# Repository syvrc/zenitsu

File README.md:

## zenitsu

> I made a zenitsu keychain that has 2 LEDs for its eyes that fade on in the dark with a photoresistor and capacitor, it also has a push button to turn the LEDs off even in the dark.  

## Schematic

# PCB
| PCB Front               | PCB Back                         |
|:-----------------------:|:--------------------------------:|
||  |

## 3d render
| Front                          | Back                          |
|:------------------------------:|:-----------------------------:|
|||

## Features
> it has photoresistor to control when LEDs will be: `ON (dark)` and `OFF (light)`  
> capacitor for a light fade effect on the LEDs  
> a toggle button switch to turn off LEDs even when dark outside  
> its a KEYCHAINN !!!

## BOM
| Component               | Qty |
| ----------------------- | --- |
| LEDs                    | 2   |
| Battery Holder          | 1   |
| Photoresistor           | 1   |
| Potentiometer           | 1   |
| 2.2M Resistor           | 1   |
| 4.7k Resistor           | 1   |
| 47k Resistor            | 1   |
| 100k Resistor           | 1   |
| 220 Resistor            | 1   |
| 470 Resistors           | 2   |
| 10uF Capacitor          | 1   |
| 470nF Capacitor         | 1   |
| Push Button             | 1   |
| NPN Transistors         | 3   |

---
> made by @syvr (on slack) 🚶‍♂️

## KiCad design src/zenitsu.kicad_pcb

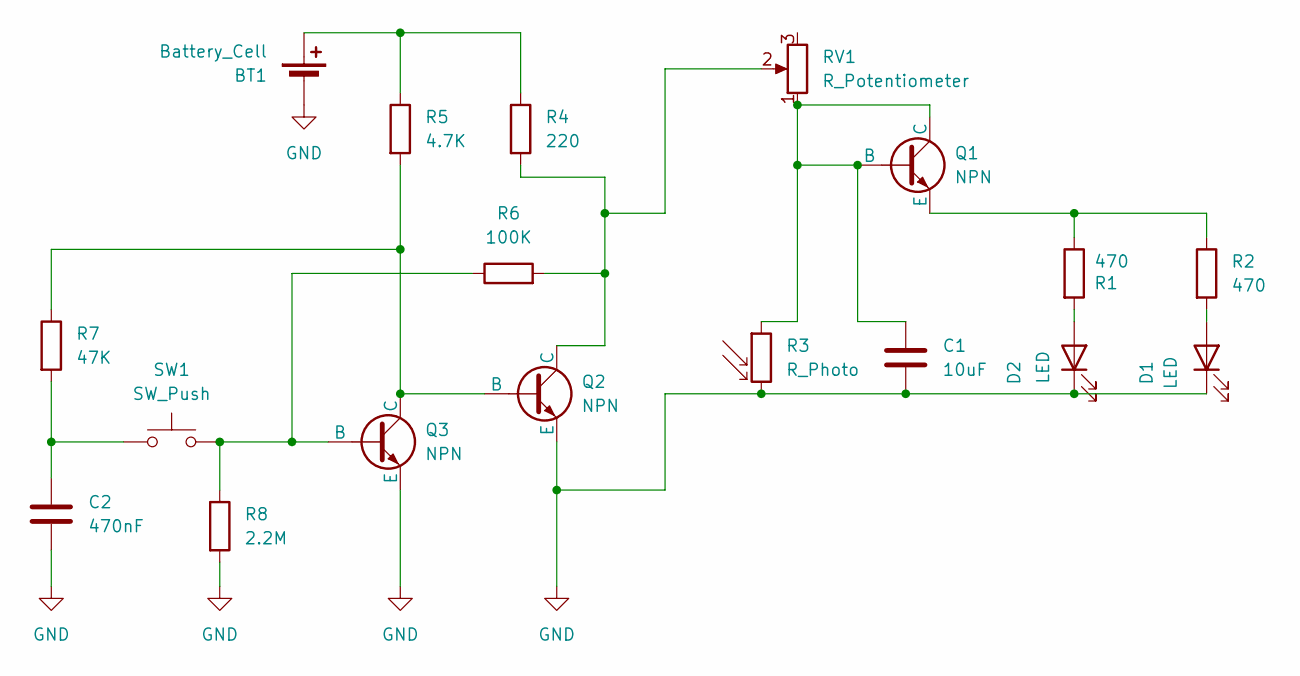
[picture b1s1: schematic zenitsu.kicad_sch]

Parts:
BT1: Battery_Cell; BatteryHolder_Keystone_3034_1x20mm
C1: 10uF; CP_Radial_D8.0mm_P5.00mm
C2: 470nF; CP_Radial_D8.0mm_P5.00mm
D1, D2: LED; LED_D5.0mm
Q1, Q2, Q3: NPN; TO-92L_HandSolder
R1, R2: 470; R_Axial_DIN0207_L6.3mm_D2.5mm_P7.62mm_Horizontal
R3: R_Photo; R_LDR_5.1x4.3mm_P3.4mm_Vertical
R4: 220; R_Axial_DIN0207_L6.3mm_D2.5mm_P7.62mm_Horizontal
R5: 4.7K; R_Axial_DIN0207_L6.3mm_D2.5mm_P7.62mm_Horizontal
R6: 100K; R_Axial_DIN0207_L6.3mm_D2.5mm_P7.62mm_Horizontal
R7: 47K; R_Axial_DIN0207_L6.3mm_D2.5mm_P7.62mm_Horizontal
R8: 2.2M; R_Axial_DIN0207_L6.3mm_D2.5mm_P7.62mm_Horizontal
RV1: R_Potentiometer; Potentiometer_Vishay_T73YP_Vertical
SW1: SW_Push; SW_PUSH_6mm

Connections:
GND: BT1.2 (-), C1.2, C2.2, D1.1 (K), D2.1 (K), Q2.3 (E), Q3.3 (E), R3.2, R8.2
unnamed: BT1.1 (+), R4.1, R5.1
unnamed: C2.1, R7.2, SW1.1
unnamed: D1.2 (A), R2.2
unnamed: D2.2 (A), R1.2
unnamed: C1.1, Q1.1 (C), Q1.2 (B), R3.1, RV1.1
unnamed: Q1.3 (E), R1.1, R2.1
unnamed: Q2.2 (B), Q3.1 (C), R5.2, R7.1
unnamed: Q2.1 (C), R4.2, R6.2, RV1.2
unnamed: Q3.2 (B), R6.1, R8.1, SW1.2

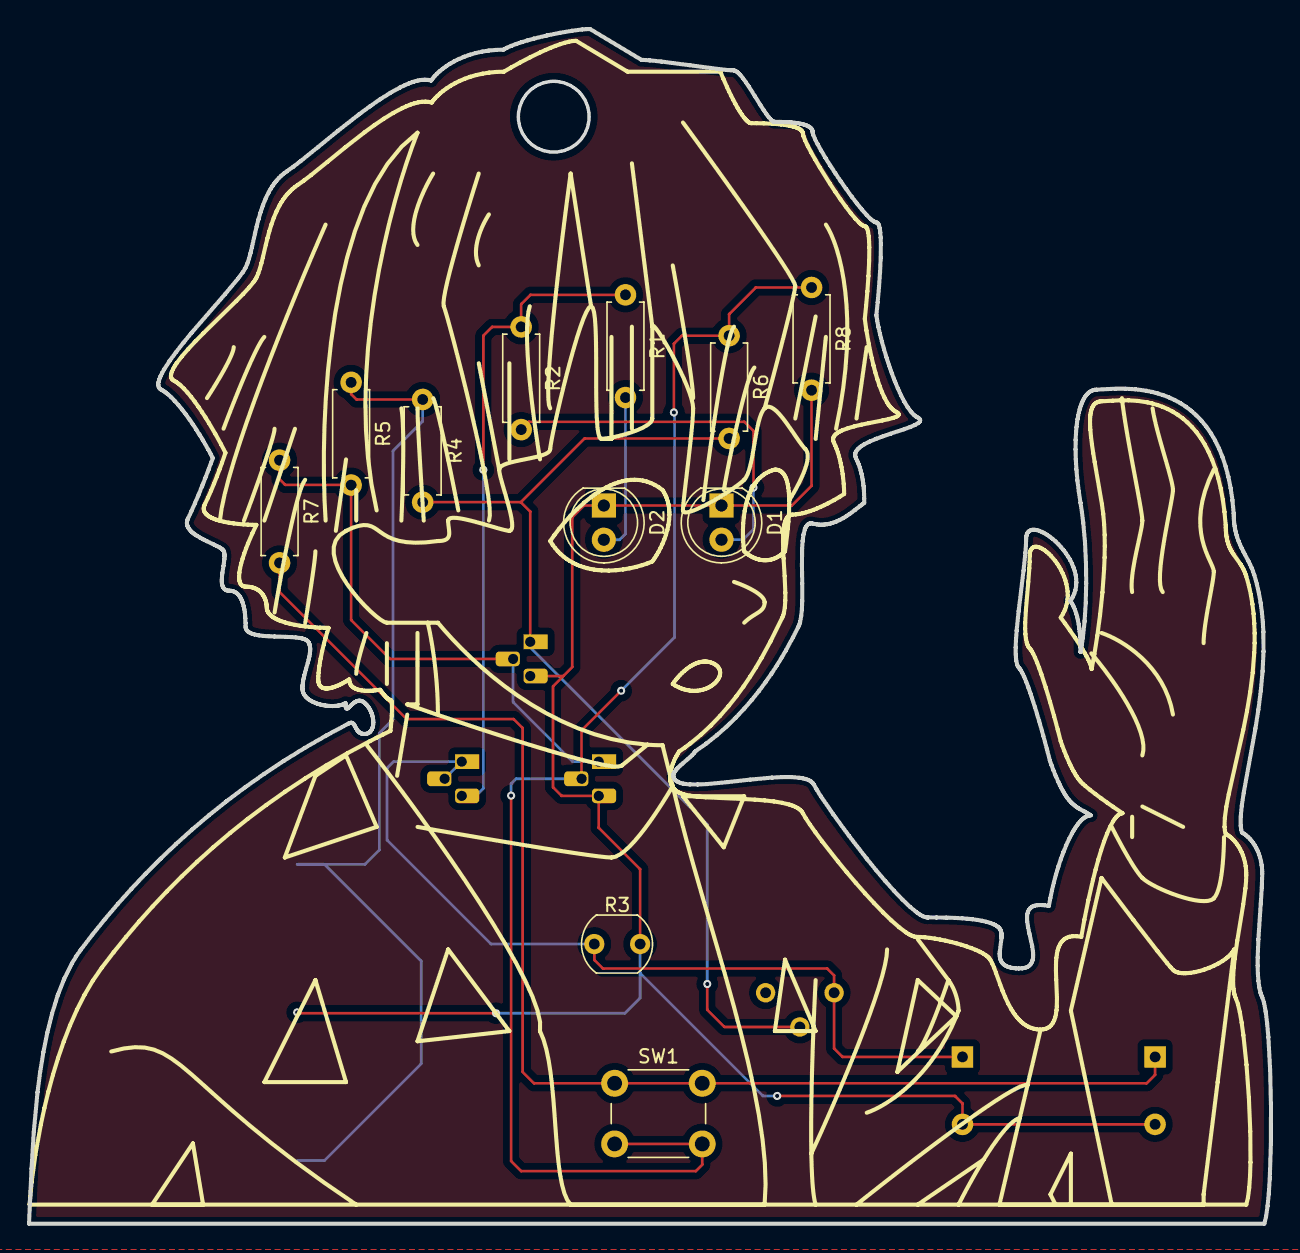
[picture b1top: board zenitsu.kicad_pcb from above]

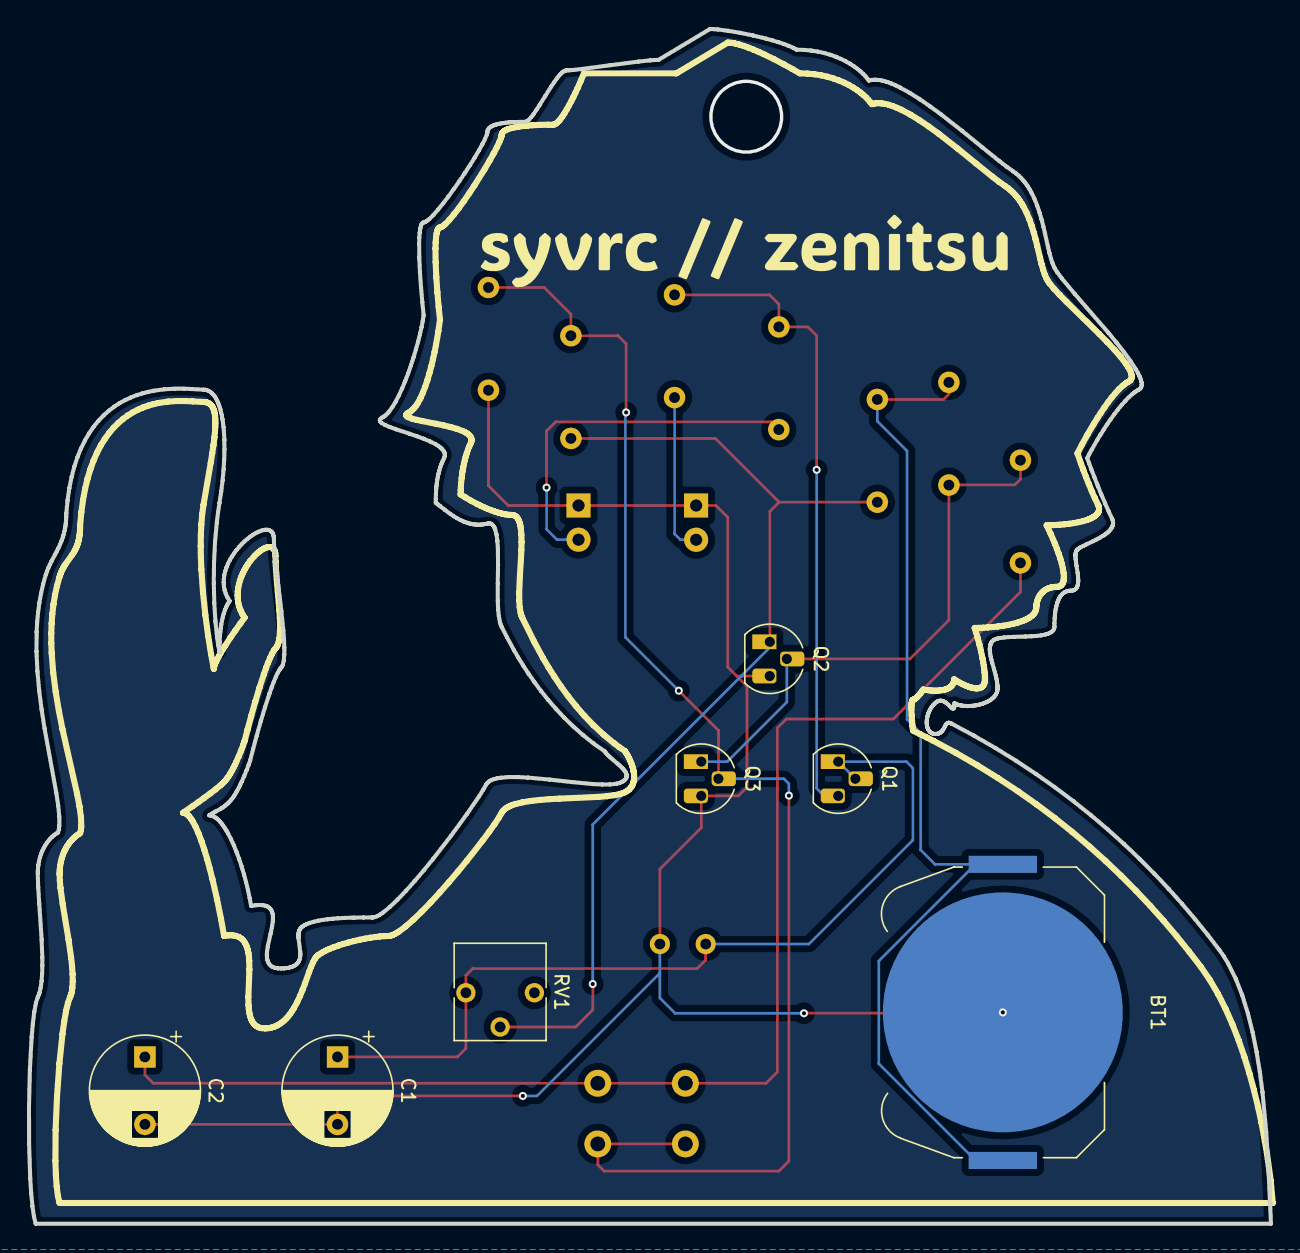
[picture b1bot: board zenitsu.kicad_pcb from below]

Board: 2 copper layers, 92.1 x 88.6 mm, 18 parts (7 on the bottom side), 10 nets.

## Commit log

2025-06-11 draft
2025-06-11 second draft
2025-06-11 third draft
2025-06-11 fourth draft
2025-06-11 final draft
